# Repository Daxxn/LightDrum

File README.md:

# LightDrum

### Have you ever wanted the drum set to be the loudest thing on stage? Well... this won't do that, but it will be extremely visible!

---

This is my dads christmas present. (I dont even remember how long it's been...) The idea is to lay strings of LEDs on his drum set and control the strings with audio and MIDI signals. With the ability to control more lighting systems through the DMX interface. The other purpose of this project is to learn. To that end, all interface libraries are written by me and are not feature complete or fully tested.

> Current Revision: `REV12`
>
> All revisions before REV8 are early prototypes and are for archival. They are not fully functional or feature complete.

# Renders

## Main PCB

## Interface PCB

## Features

### Output
- 8 Individual LED String Channels
- 1 Amp Rating per Channel
- DMX (RS-485) Interface

## Input
- 1/8" jack Audio
- XLR Balanced Audio
- MIDI
- DMX (RS-485) Interface

## PWM channels

The 8 individual RGB channels are controlled with 3 [PCA9634.](https://www.nxp.com/docs/en/data-sheet/PCA9634.pdf) Providing 8-bit PWM steps per channel with overall brightness and multiplexing.

## Bulk Lighting

The new automitive ECU connector has allowed for more pins, hense, some extra features. This includes 3 linear LED drivers for white COB LEDs. These are very bright and can either be controlled through the user interface, MIDI, or audio.

## Power Management

Each channel includes current monitoring with a high-side power override. This is all to avoid shorts and over-current conditions on the high current 12V supply. Both barrel jacks will need to be used for the LEDs to be activated. Due the large amount of power required, one barrel jack would probably melt.

## Audio Processing

The PCM1821 dual channel 32bit audio ADC handles the audio conversion and is sent to the MCU via I2S. Theres some minor filtering and impedance matching in the analog front-end. However, most of the audio processing will be handled in software.

## User Interface

- 3.2" TFT LCD Display
- Navigation Hat Switch for menu navigation
- Bar Graphs for display of audio levels and current load (or anything else I can think of.)
- 2 Contextual Rotary Encoders
- AND; a reset switch. For when things go horribly wrong.
- MicroSD card slot for loading lighting profiles and other options by the user.

The display contains a full menu to select modes, configure options, and IO. I'm using a Nextion display and their GUI editor for all the menuing. Its not the most performant display but it does allow for easy integration of a reasonably high res, full color screen.

In the future, Im planning to upgrade to a faster STM32 MCU, something like an F7, H5, or H7. Taking advantage of the TouchGFX GUI design software and integrate the screen control into the main MCU. Even with the faster MCU, it will be cheaper and increase screen performance, due to the removal of the Nextion display.

---

## Documentation

- [Docs](./Docs/)

- [Interactive BOMs](./Docs/BOMs/REV10/)

- TODO: Link to a user manual and theory of operation doc.

---

## Firmware installation

### Hardware Requirements

The old firmware was built with the Arduino Framework. The new MCU will be using the ST IDE, toolchain, and HAL (Hardware Abstraction Layer) along with the other required libraries. Im using the STLink programmer due to the much better performance and debugging than the ATTiny USB programmer.

### OLD PIO Configuration

[env:megaUSB] : Uses the built-in programmer. This is only used for the older revisions. (REV1 & REV2)

[env:megaICSP] : Main programming method. Using the ATTiny USB programmer.

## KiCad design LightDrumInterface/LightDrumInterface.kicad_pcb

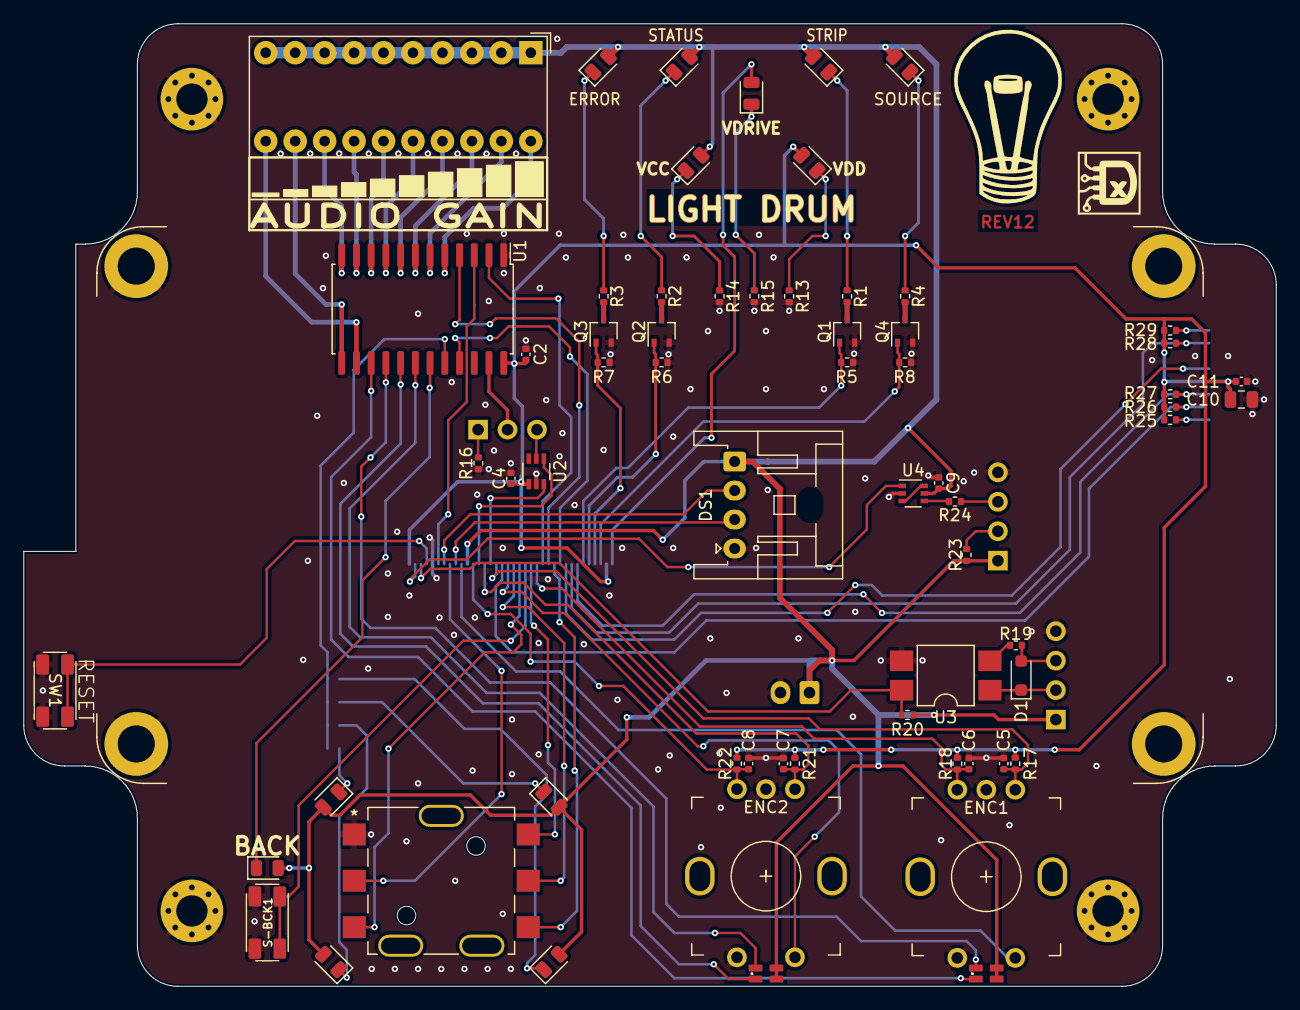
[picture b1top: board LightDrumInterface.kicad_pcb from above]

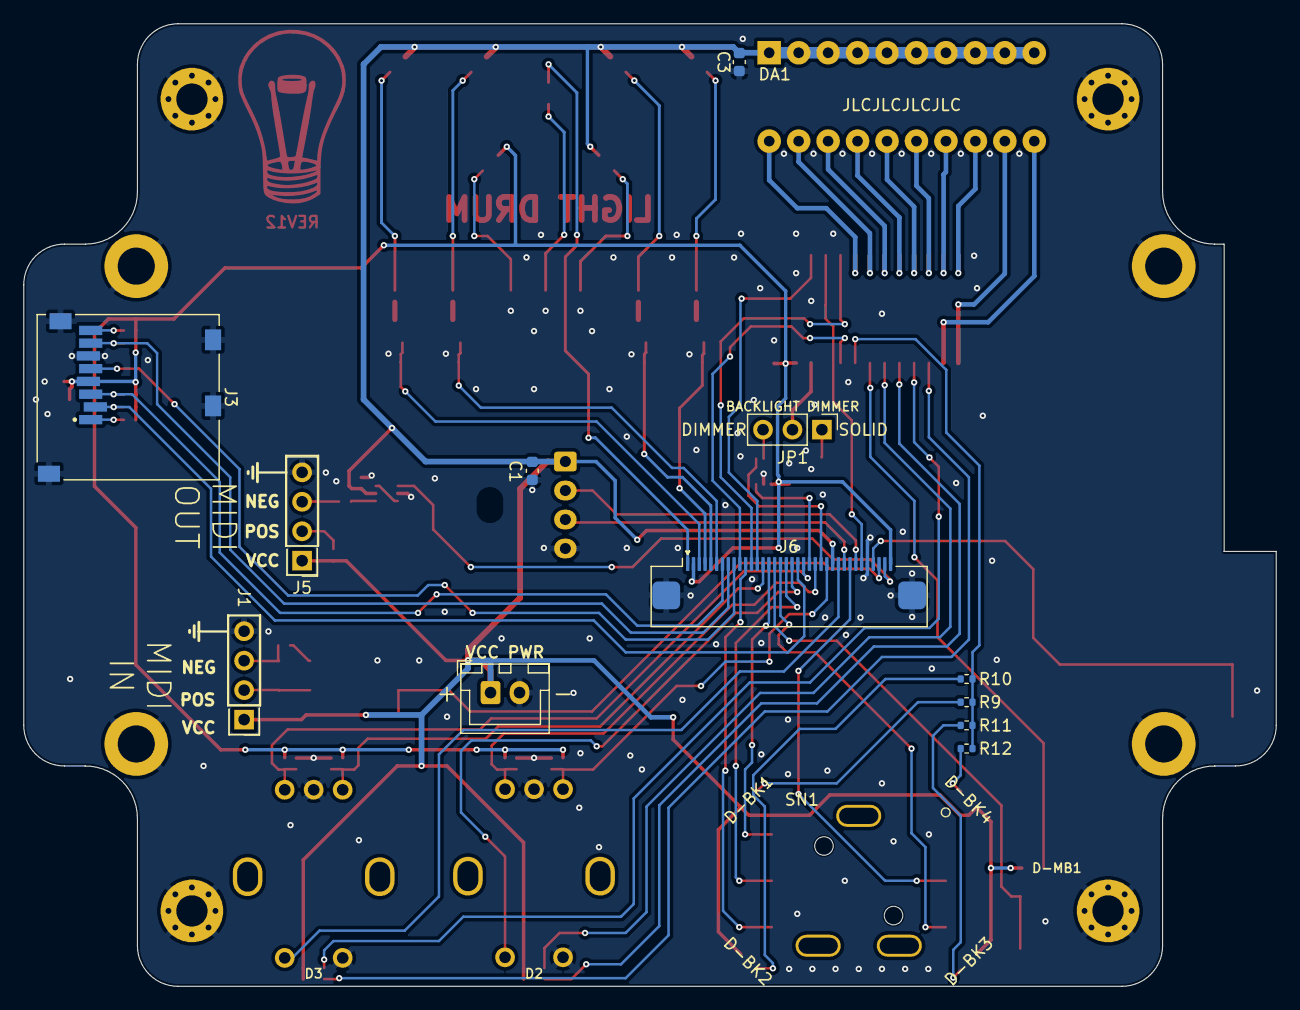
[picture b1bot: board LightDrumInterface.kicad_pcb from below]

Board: 2 copper layers, 108.0 x 83.0 mm, 81 parts (12 on the bottom side), 78 nets.

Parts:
C1, C3: 1uF; C_0603_1608Metric
C2, C4, C5, C6, C7, C8, C9, C11: 100nF; C_0402_1005Metric
C10: 4.7uF; C_0805_2012Metric
D1: 1N4448; D_SOD-323_HandSoldering
D2, D3: APHBM2012QBDSURKC; APHBM-2012
D-AUDIO-SEL1: GREEN; LED_0805_2012Metric
D-BK1, D-BK2, D-BK3, D-BK4: RED; LED_0805_2012Metric
D-DBG1: RED; LED_0805_2012Metric
D-MB1: RED; LED_0805_2012Metric
D-STA1: AMBER; LED_0805_2012Metric
D-STRIP-EN1: GREEN; LED_0805_2012Metric
D-VCC1: BLUE; LED_0805_2012Metric
D-VDD1: BLUE; LED_0805_2012Metric
D-VDRIVE1: BLUE; LED_0805_2012Metric
DA1: LTA-1000HR; HDSP-48xx
DS1: NX4024K032; NX4024K032-RA-S04B
ENC1: Encoder1; PEC11R
ENC2: Encoder2; PEC11R
ENCLOSURE1: LeMotech_Black_ENC-115x90
H1, H2, H3, H4: M2.5; MountingHole_2.7mm_M2.5_Pad_Via
J1: MIDI-IN; PinHeader_1x04_P2.54mm_Vertical
J3: Micro_SD_Card; MEM2061-01-188-00-A
J4: PWR-CONN; JST_XH_B2B-XH-A_Vertical
J5: MIDI-OUT; PinHeader_1x04_P2.54mm_Vertical
J6: 0541323662
JP1: BRT-JMP; PinHeader_1x03_P2.54mm_Vertical
Q1, Q2, Q3, Q4: NX6008NBKWX; SOT-323_SC-70
R1, R4: 100; R_0402_1005Metric
R2, R14, R16: 560; R_0402_1005Metric
R3: 620; R_0402_1005Metric
R5, R6, R7, R8, R17, R18, R20, R21, R22: 10K; R_0402_1005Metric
R9, R10, R11, R12: 300; R_0402_1005Metric
R13: 1.3K; R_0402_1005Metric
R15: 4.7K; R_0402_1005Metric
R19, R23, R24: 220; R_0402_1005Metric
R25, R26, R27, R28, R29: 47K; R_0402_1005Metric
S-BCK1: M-BACK; TL3365AF180QG
SN1: JS5208
SW1: RESET-SW; TL3365AF180QG
U1: STP16CP05; SOIC-24W_7.5x15.4mm_P1.27mm
U2: TPL0401B-10-Q1; Texas_R-PDSO-G6
U3: APC-817A1-SL; SMDIP-4_W7.62mm
U4: 74LVC2G14GW; SOT-363_SC-70-6

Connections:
/AUDIO-SRC-IND: J6.3, Q4.1 (G), R8.1
/DIAG-DEBUG: J6.4, Q3.1 (G), R7.1
/DIAG-STATUS: J6.5, Q2.1 (G), R6.1
/ENC1-A: C5.1, ENC1.A, J6.21, R17.1
/ENC1-B: C6.2, ENC1.B, J6.14, R18.2
/ENC1-SW: ENC1.S1, J6.27
/ENC2-A: C7.1, ENC2.A, J6.23, R21.1
/ENC2-B: C8.2, ENC2.B, J6.25, R22.2
/ENC2-SW: ENC2.S1, J6.19
/GRAPH-CLK: J6.31, U1.3 (CLK)
/GRAPH-LE: J6.12, U1.4 (LE/DM1)
/GRAPH-SDI: J6.13, U1.2 (SDI)
/GRAPH-~OE: J6.10, U1.21 (~OE/DM2)
/I2C-SCLK: J6.22, U2.3 (SCL)
/I2C-SDA: J6.24, U2.4 (SDA)
/MENU-ACT: J6.17, SN1.3 (PUSH)
/MENU-BACK: J6.16, S-BCK1.2 (B)
/MENU-DOWN: J6.11, SN1.6 (DOWN)
/MENU-LEFT: J6.29, SN1.2 (LEFT)
/MENU-RIGHT: J6.18, SN1.5 (RIGHT)
/MENU-UP: J6.15, SN1.4 (UP)
/MIDI-IN: J6.34, R20.1, U3.4
/MIDI-OUT: J6.35, U4.1 (1A)
/NAV-BACKLIGHT: R9.2, R10.2, R11.2, R12.2, U1.20 (~OUT15)
/R-EXT: JP1.2 (C), U1.23 (R-EXT)
/SCR-RX: DS1.3 (RX), J6.28
/SCR-TX: DS1.2 (TX), J6.30
/SD-CD: J3.2 (DAT3/CD), J6.20, R26.2
/SD-CLK: J3.5 (CLK), J6.9
/SD-CMD: J3.3 (CMD), J6.7, R27.2
/SD-D0: J3.7 (DAT0), J6.8, R28.2
/STRIP-PWR: J6.6, Q1.1 (G), R5.1
/~RESET: J6.33, SW1.2 (B)
GND: C1.2, C2.2, C3.2, C4.2, C5.2, C6.1, C7.2, C8.1, C9.2, C10.2, C11.2, DS1.4 (GND), ENC1.C, ENC1.S2, ENC2.C, ENC2.S2, H1.1, H2.1, H3.1, H4.1, J1.4, J3.6 (VSS), J3.9 (SHIELD), J4.2, J5.4, J6.32, J6.M (MNT), Q1.2 (S), Q2.2 (S), Q3.2 (S), Q4.2 (S), R5.2, R6.2, R7.2, R8.2, R13.2, R14.2, R15.2, R16.2, S-BCK1.1 (A), SN1.1 (COM), SW1.1 (A), U1.1 (GND), U2.2 (GND), U3.3, U4.2 (GND)
unnamed: D1.2 (A), J1.3, R19.1
unnamed: D1.1 (K), J1.2, U3.1
unnamed: D2.2 (B-K), U1.17 (~OUT12)
unnamed: D2.3 (R-K), U1.18 (~OUT13)
unnamed: D3.2 (B-K), U1.15 (~OUT10)
unnamed: D3.3 (R-K), U1.16 (~OUT11)
unnamed: D-AUDIO-SEL1.1 (K), R4.1
unnamed: D-BK1.1 (K), R9.1
unnamed: D-BK2.1 (K), R10.1
unnamed: D-BK3.1 (K), R11.1
unnamed: D-BK4.1 (K), R12.1
unnamed: D-DBG1.1 (K), R3.1
unnamed: D-MB1.1 (K), U1.19 (~OUT14)
unnamed: D-STA1.1 (K), R2.1
unnamed: D-STRIP-EN1.1 (K), R1.1
unnamed: D-VCC1.1 (K), R14.1
unnamed: D-VDD1.1 (K), R13.1
unnamed: D-VDRIVE1.1 (K), R15.1
unnamed: J3.8 (DAT1), R29.2
unnamed: J3.1 (DAT2), R25.2
unnamed: J5.2, R23.1
unnamed: J5.3, R24.1
unnamed: JP1.1 (A), R16.1
unnamed: JP1.3 (B), U2.5 (W)
unnamed: Q1.3 (D), R1.2
unnamed: Q2.3 (D), R2.2
unnamed: Q3.3 (D), R3.2
unnamed: Q4.3 (D), R4.2
unnamed: R19.2, U3.2
unnamed: DA1.20, U1.5 (~OUT0)
unnamed: DA1.19, U1.6 (~OUT1)
unnamed: DA1.18, U1.7 (~OUT2)
unnamed: DA1.17, U1.8 (~OUT3)
unnamed: DA1.16, U1.9 (~OUT4)
unnamed: DA1.15, U1.10 (~OUT5)
unnamed: DA1.14, U1.11 (~OUT6)
unnamed: DA1.13, U1.12 (~OUT7)
unnamed: DA1.12, U1.13 (~OUT8)
unnamed: DA1.11, U1.14 (~OUT9)
unnamed: U4.3 (2A), U4.6 (1Y)
unnamed: R24.2, U4.4 (2Y)
VCC: C1.1, C3.1, C9.1, D2.1 (B-A), D2.4 (R-A), D3.1 (B-A), D3.4 (R-A), D-AUDIO-SEL1.2 (A), D-BK1.2 (A), D-BK2.2 (A), D-BK3.2 (A), D-BK4.2 (A), D-DBG1.2 (A), D-MB1.2 (A), D-STA1.2 (A), D-STRIP-EN1.2 (A), D-VCC1.2 (A), DA1.1, DA1.2, DA1.3, DA1.4, DA1.5, DA1.6, DA1.7, DA1.8, DA1.9, DA1.10, DS1.1 (VCC), J1.1, J4.1, J5.1, J6.26, R20.2, R23.2, U4.5 (VCC)
VDD: C2.1, C4.1, C10.1, C11.1, D-VDD1.2 (A), J3.4 (VDD), J6.2, J6.36, R17.2, R18.1, R21.2, R22.1, R25.1, R26.1, R27.1, R28.1, R29.1, U1.24 (VDD), U2.1 (VDD)
Vdrive: D-VDRIVE1.2 (A), J6.1

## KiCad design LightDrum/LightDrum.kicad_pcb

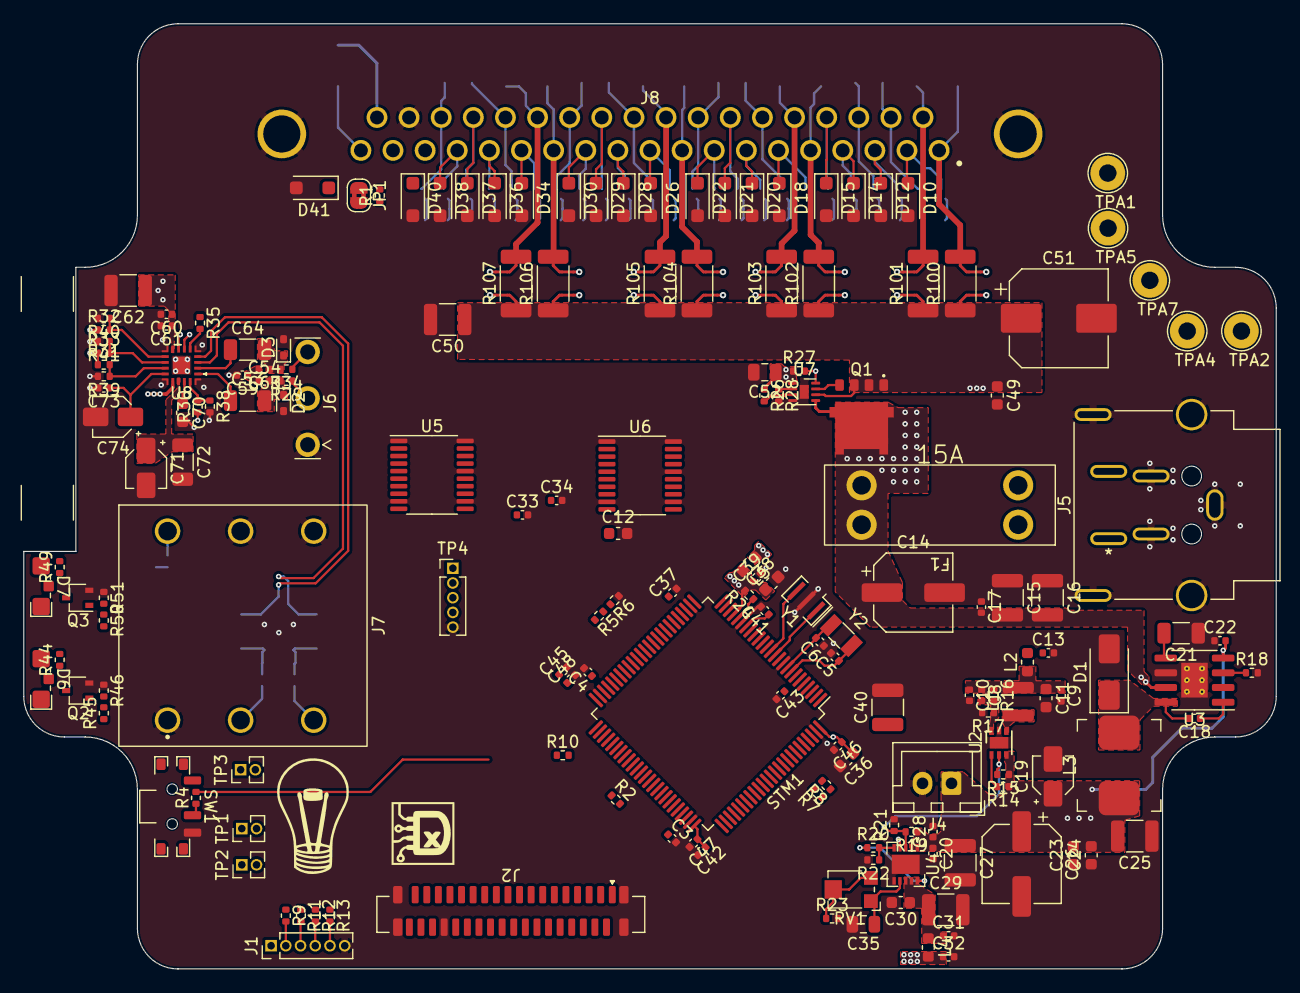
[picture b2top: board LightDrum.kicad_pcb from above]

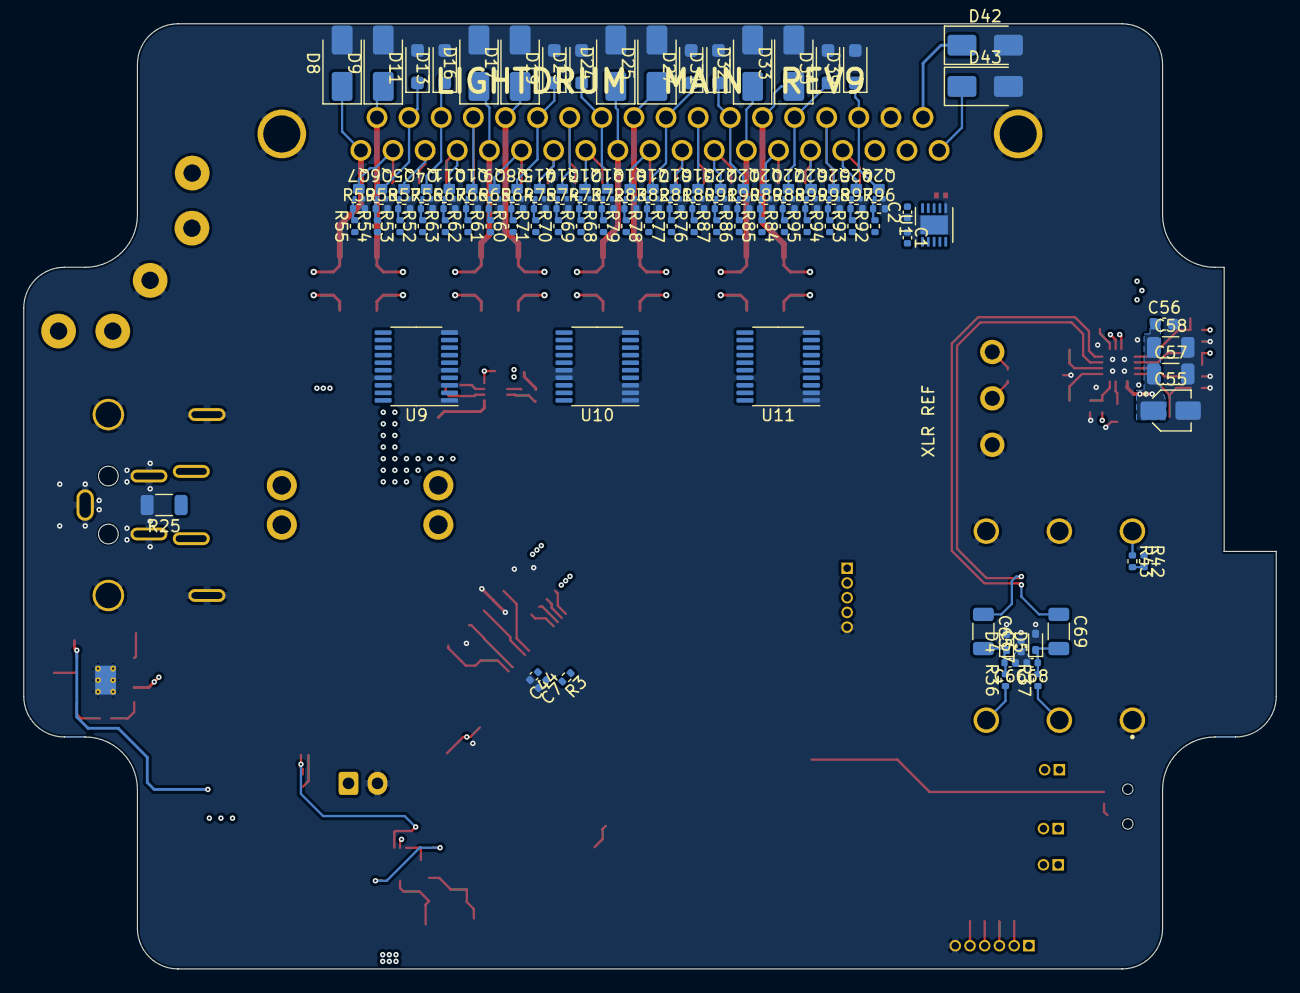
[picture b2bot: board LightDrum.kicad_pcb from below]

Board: 4 copper layers, 108.0 x 81.5 mm, 305 parts (115 on the bottom side), 209 nets.

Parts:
C1, C2, C7, C9, C10, C13, C17, C20, C22, C28, C31, C32, C33, C34, C37, C39, C41, C42, C43, C44, C45, C46, C47, C48, C60, C61, C73: 100nF; C_0402_1005Metric
C3, C4: 2.2uF; C_0402_1005Metric
C5, C6: 15pF; C_0402_1005Metric
C8: 22pF; C_0402_1005Metric
C11, C12, C23, C24, C30, C36, C38, C49, C56, C70: 1uF; C_0603_1608Metric
C14: 47uF; CP_Elec_6.3x7.7
C15, C16, C25, C27, C29, C40, C50, C62: 10uF; C_1210_3225Metric
C18: 10nF; C_0402_1005Metric
C19, C55, C71, C74: 10uF; CP_Elec_3x5.4
C21, C53, C64, C65, C69: 220nF; C_1206_3216Metric
C26: 100uF; CP_Elec_6.3x5.2
C35, C52: 4.7uF; C_0805_2012Metric
C51: 220uF; CP_Elec_8x10
C54, C63, C66, C68: 470pF; C_0402_1005Metric
C57, C58, C72: 100nF C0G; C_1206_3216Metric
C59, C67: 47pF; C_0402_1005Metric
D1: SK36AHE3; D_SMA
D2, D3, D4, D5: CEZ5V6; D_SOD-523
D6: HP IND - BLUE; LTST-S321TBKT
D7: XLR IND - BLUE; LTST-S321TBKT
D8, D9, D16, D17, D24, D25, D32, D33, D42, D43: SMAJ14CA; D_SMA
D10, D11, D12, D13, D14, D15, D18, D19, D20, D21, D22, D23, D26, D27, D28, D29, D30, D31, D34, D35, D36, D37, D38, D39, D40, D41: SMF4L13CA; D_SOD-123F
ENC0: LeMotech_Black_ENC-115x90
F1: 15A; 3557-10
J1: SWD CONN; PinHeader_1x06_P1.27mm_Vertical
J2: 0525593652
J4: PWR-CONN; JST_XH_B2B-XH-A_Vertical
J5: DIN-4-SH; KPJXHT-4S-S
J6: XLR3; CP30082-XLR
J7: SJ-63073E
J8: LED D-SUB; DSUB-37-182-037-113R531
JP1: DMX-RT-JUMP; SolderJumper-2_P1.3mm_Bridged2Bar_RoundedPad1.0x1.5mm
L1: 2.2uH; LQH3NPN
L2, L4, L5: 100nH; L_0603_1608Metric
L3: 22uH; PA4341
Q1: NTMFS5C430NLT1G; POWER-FET-5-DFN
Q2, Q3: NX6008NBKWX; SOT-323_SC-70
Q4, Q5, Q6, Q7, Q8, Q9, Q10, Q11, Q12, Q13, Q14, Q15, Q16, Q17, Q18, Q19, Q20, Q21, Q22, Q23, Q24, Q25, Q26, Q27: PMXB43UNEZ; DFN1010D-3
R1: 120; R_0402_1005Metric
R2, R10: 2.2K; R_0402_1005Metric
R3, R4, R5, R6, R26, R27, R28, R30, R31, R32, R33, R38, R39, R40, R41, R46, R51, R56, R57, R58, R59, R64, R65, R66, R67, R72, R73, R74, R75, R80, R81, R82, R83, R88, R89, R90, R91, R96, R97, R98, R99: 10K; R_0402_1005Metric
R7, R8: 4.7K; R_0402_1005Metric
R9, R11, R12, R13, R29, R34, R35, R36, R37: 22; R_0402_1005Metric
R14, R15, R17, R21, R42: 100K; R_0402_1005Metric
R16: 430K; R_0402_1005Metric
R18: 15K; R_0402_1005Metric
R19: 1.54M; R_0402_1005Metric
R20: 402K; R_0402_1005Metric
R22: 33K; R_0402_1005Metric
R23: 20K; R_0402_1005Metric
R24: 47; R_0402_1005Metric
R25: 10K; R_1206_3216Metric
R43, R45, R50, R52, R53, R54, R55, R60, R61, R62, R63, R68, R69, R70, R71, R76, R77, R78, R79, R84, R85, R86, R87, R92, R93, R94, R95: 100; R_0402_1005Metric
R44, R49: 1K; R_0402_1005Metric
R100, R101, R102, R103, R104, R105, R106, R107: 50m; R_2010_5025Metric
RV1: 4.7K; Bourns_TC33X
STM1: STM32F412VET3; LQFP-100_14x14mm_P0.5mm
SW1: BOOT0; PCM12SMTR
T1, T2, T3, T4, T5, T6, T7, T8, T9, T10, T11, T12, T13, T14, T15, T16: NET-TIE; NetTie-2_SMD_Pad0.25mm
TP1, TP2: I2C TP; PinHeader_1x02_P1.27mm_Vertical
TP3: MIDI TP; PinHeader_1x02_P1.27mm_Vertical
TP4: I2S TP; PinHeader_1x05_P1.27mm_Vertical
TPA1: VDRIVE TP; TestPoint_Loop_D2.54mm_Drill1.5mm_Beaded
TPA2: VCC TP; TestPoint_Loop_D2.54mm_Drill1.5mm_Beaded
TPA4: VDD TP; TestPoint_Loop_D2.54mm_Drill1.5mm_Beaded
TPA5: VDDA TP; TestPoint_Loop_D2.54mm_Drill1.5mm_Beaded
TPA7: GND TP; TestPoint_Loop_D2.54mm_Drill1.5mm_Beaded
U1: STR485; DFN-10-1EP_3x3mm_P0.5mm_EP1.65x2.38mm
U2: AP3401; DFN-6-1EP_2x2mm_P0.65mm_EP1x1.6mm
U3: LM22673-5V; SOIC-8-1EP_3.9x4.9mm_P1.27mm_EP2.29x3mm_ThermalVias
U4: TPS7A94; WSON-10-1EP_3x3mm
U5, U6: INA4181 A2; TSSOP-20_4.4x6.5mm_P0.65mm
U7: SLG55021; TDFN-8-1EP_2x2mm_P0.5mm_EP0.8x1.2mm
U8: PCM1821; TI-WQFN-RTE_(CUSTOM)-20-3x3mm-P0.5mm-EP1_1.4mm
U9, U10, U11: PCA9634_TSSOP20; TSSOP-20_4.4x6.5mm_P0.65mm
Y1: 16MHz; Resonator_SMD_Murata_CSTxExxV-3Pin_3.0x1.1mm
Y2: 32.768KHz; Crystal_SMD_3215-2Pin_3.2x1.5mm

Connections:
+12V: C14.1, C15.2, C16.2, C17.2, F1.2, Q1.5 (D), U3.7 (VIN), U7.5 (D)
/AUDIO INPUTS/JACK+: C65.2, C66.2, D4.1 (K), R36.2
/AUDIO INPUTS/JACK-: C68.1, C69.2, D5.1 (K), R37.2
/AUDIO INPUTS/JACK-IN+: C65.1, U8.3 (IN2+)
/AUDIO INPUTS/JACK-IN-: C69.1, U8.4 (IN2-)
/AUDIO INPUTS/JACK-SW: R42.2, R43.2
/AUDIO INPUTS/XLR+: C53.2, C54.2, D2.1 (K), R29.2
/AUDIO INPUTS/XLR-: C63.1, C64.2, D3.1 (K), R34.2
/AUDIO INPUTS/XLR-IN+: C53.1, U8.1 (IN1+)
/AUDIO INPUTS/XLR-IN-: C64.1, U8.2 (IN1-)
/AUDIO-SRC-IND_{PWM}: J2.3, STM1.4 (TIM9-CH1)
/DIAG-DEBUG_{PWM}: J2.4, STM1.65 (TIM3-CH3)
/DIAG-STATUS_{PWM}: J2.5, STM1.66 (TIM3-CH4)
/DMX+: D40.1 (K), J8.17, R1.2, U1.9 (B)
/DMX-: D41.1 (K), J8.18, JP1.1 (A), U1.8 (A)
/DMX-EN: U1.3 (DE), U1.4 (~RE)
/ENC1-B: J2.10, STM1.85 (PD4)
/ENC2-B: J2.25, STM1.51 (PB12)
/FI2C-SCLK_{S}: R10.2, STM1.54 (I2CFMP1-SCL), TP2.1, U9.18 (SCLK), U9.19 (SDA), U10.18 (SCLK), U11.18 (SCLK)
/FI2C-SDA_{S}: R2.2, STM1.64 (I2CFMP1-SDA), TP2.2, U10.19 (SDA), U11.19 (SDA)
/GRAPH-CLK_{S}: J2.29, STM1.43 (SPI4-SCK)
/GRAPH-LE_{S}: J2.14, STM1.60 (PD13)
/GRAPH-SDI_{S}: J2.31, STM1.5 (SPI4-COPI)
/GRAPH-~OE_{S}: J2.12, STM1.62 (PD15)
/HP-SEL-IND_{PWM}: R45.2, STM1.24 (TIM2-CH2)
/I2C-SCLK_{S}: J2.20, R7.2, STM1.92 (I2C1-SCL), TP1.1
/I2C-SDA_{S}: J2.23, R8.2, STM1.93 (I2C1-SDA), TP1.2
/I2S-CK_{S}: STM1.78 (I2S3-CK), TP4.2, U8.7 (BCLK)
/I2S-SD_{S}: R35.1, STM1.87 (I2S3-SD), TP4.3
/I2S-WS_{S}: STM1.77 (I2S3-WS), TP4.4, U8.8 (FSYNC)
/MICROCONTROLLER/BOOT0_{D}: R4.2, STM1.94 (BOOT0)
/MICROCONTROLLER/BOOT1_{D}: R5.1, R6.2, STM1.37 (BOOT1)
/MICROCONTROLLER/XTAL1: STM1.12 (OSC-IN), Y1.1
/MICROCONTROLLER/XTAL2: STM1.13 (OSC-OUT), Y1.3
/MIDI-IN_{S}: J2.32, STM1.26 (USART2-RX), TP3.1
/MIDI-OUT_{S}: J2.35, STM1.25 (USART2-TX), TP3.2
/POWER/PS-SW_: C18.2, D1.1 (K), L3.1, U3.8 (SW)
/POWER/VREF+: R24.1, STM1.21 (VREF+)
/PWM-~OE_{PWM}: STM1.63 (TIM3-CH1), U9.15 (~OE), U10.15 (~OE), U11.15 (~OE)
/RGB CONTROL/RGB Control 1/LED1-B: D14.1 (K), J8.4, Q11.3 (D)
/RGB CONTROL/RGB Control 1/LED1-B-SIG: R63.1, U9.6 (LED0)
/RGB CONTROL/RGB Control 1/LED1-G: D10.1 (K), J8.2, Q7.3 (D)
/RGB CONTROL/RGB Control 1/LED1-G-SIG: R55.1, U9.14 (LED7)
/RGB CONTROL/RGB Control 1/LED1-R: D12.1 (K), J8.3, Q5.3 (D)
/RGB CONTROL/RGB Control 1/LED1-R-SIG: R53.1, U9.12 (LED5)
/RGB CONTROL/RGB Control 1/LED2-G: D18.1 (K), J8.6, Q9.3 (D)
/RGB CONTROL/RGB Control 1/LED2-G-SIG: R61.1, U9.8 (LED2)
/RGB CONTROL/RGB Control 1/LED5-B: D15.1 (K), J8.23, Q10.3 (D)
/RGB CONTROL/RGB Control 1/LED5-B-SIG: R62.1, U9.7 (LED1)
/RGB CONTROL/RGB Control 1/LED5-G: D11.1 (K), J8.21, Q6.3 (D)
/RGB CONTROL/RGB Control 1/LED5-G-SIG: R54.1, U9.13 (LED6)
/RGB CONTROL/RGB Control 1/LED5-R: D13.1 (K), J8.22, Q4.3 (D)
/RGB CONTROL/RGB Control 1/LED5-R-SIG: R52.1, U9.11 (LED4)
/RGB CONTROL/RGB Control 1/LED6-G: D19.1 (K), J8.25, Q8.3 (D)
/RGB CONTROL/RGB Control 1/LED6-G-SIG: R60.1, U9.9 (LED3)
/RGB CONTROL/RGB Control 2/LED2-B: D22.1 (K), J8.8, Q13.3 (D)
/RGB CONTROL/RGB Control 2/LED2-B-SIG: R69.1, U10.12 (LED5)
/RGB CONTROL/RGB Control 2/LED2-R: D20.1 (K), J8.7, Q15.3 (D)
/RGB CONTROL/RGB Control 2/LED2-R-SIG: R71.1, U10.14 (LED7)
/RGB CONTROL/RGB Control 2/LED3-G: D26.1 (K), J8.10, Q19.3 (D)
/RGB CONTROL/RGB Control 2/LED3-G-SIG: R79.1, U10.6 (LED0)
/RGB CONTROL/RGB Control 2/LED3-R: D28.1 (K), J8.11, Q17.3 (D)
/RGB CONTROL/RGB Control 2/LED3-R-SIG: R77.1, U10.8 (LED2)
/RGB CONTROL/RGB Control 2/LED6-B: D23.1 (K), J8.27, Q12.3 (D)
/RGB CONTROL/RGB Control 2/LED6-B-SIG: R68.1, U10.11 (LED4)
/RGB CONTROL/RGB Control 2/LED6-R: D21.1 (K), J8.26, Q14.3 (D)
/RGB CONTROL/RGB Control 2/LED6-R-SIG: R70.1, U10.13 (LED6)
/RGB CONTROL/RGB Control 2/LED7-G: D27.1 (K), J8.29, Q18.3 (D)
/RGB CONTROL/RGB Control 2/LED7-G-SIG: R78.1, U10.7 (LED1)
/RGB CONTROL/RGB Control 2/LED7-R: D29.1 (K), J8.30, Q16.3 (D)
/RGB CONTROL/RGB Control 2/LED7-R-SIG: R76.1, U10.9 (LED3)
/RGB CONTROL/RGB Control 3/LED3-B: D30.1 (K), J8.12, Q23.3 (D)
/RGB CONTROL/RGB Control 3/LED3-B-SIG: R87.1, U11.14 (LED7)
/RGB CONTROL/RGB Control 3/LED4-B: D38.1 (K), J8.16, Q25.3 (D)
/RGB CONTROL/RGB Control 3/LED4-B-SIG: R93.1, U11.8 (LED2)
/RGB CONTROL/RGB Control 3/LED4-G: D34.1 (K), J8.14, Q21.3 (D)
/RGB CONTROL/RGB Control 3/LED4-G-SIG: R85.1, U11.12 (LED5)
/RGB CONTROL/RGB Control 3/LED4-R: D36.1 (K), J8.15, Q27.3 (D)
/RGB CONTROL/RGB Control 3/LED4-R-SIG: R95.1, U11.6 (LED0)
/RGB CONTROL/RGB Control 3/LED7-B: D31.1 (K), J8.31, Q22.3 (D)
/RGB CONTROL/RGB Control 3/LED7-B-SIG: R86.1, U11.13 (LED6)
/RGB CONTROL/RGB Control 3/LED8-B: D39.1 (K), J8.35, Q24.3 (D)
/RGB CONTROL/RGB Control 3/LED8-B-SIG: R92.1, U11.9 (LED3)
/RGB CONTROL/RGB Control 3/LED8-G: D35.1 (K), J8.33, Q20.3 (D)
/RGB CONTROL/RGB Control 3/LED8-G-SIG: R84.1, U11.11 (LED4)
/RGB CONTROL/RGB Control 3/LED8-R: D37.1 (K), J8.34, Q26.3 (D)
/RGB CONTROL/RGB Control 3/LED8-R-SIG: R94.1, U11.7 (LED1)
/RGB CONTROL/Strip Connector/STRIP-PWR1: D8.1 (K), J8.1, R100.2, T1.2
/RGB CONTROL/Strip Connector/STRIP-PWR2: D16.1 (K), J8.5, R102.2, T5.2
/RGB CONTROL/Strip Connector/STRIP-PWR3: D24.1 (K), J8.9, R104.2, T9.2
/RGB CONTROL/Strip Connector/STRIP-PWR4: D32.1 (K), J8.13, R106.2, T13.2
/RGB CONTROL/Strip Connector/STRIP-PWR5: D9.1 (K), J8.20, R101.2, T2.2
/RGB CONTROL/Strip Connector/STRIP-PWR6: D17.1 (K), J8.24, R103.2, T6.2
/RGB CONTROL/Strip Connector/STRIP-PWR7: D25.1 (K), J8.28, R105.2, T10.2
/RGB CONTROL/Strip Connector/STRIP-PWR8: D33.1 (K), J8.32, R107.2, T14.2
/RGB CONTROL/Strip Current Monitors/S1-CURR+: T3.2, U6.6 (IN+)
/RGB CONTROL/Strip Current Monitors/S1-CURR-: T1.1, U6.7 (IN-)
/RGB CONTROL/Strip Current Monitors/S2-CURR+: T7.2, U6.17 (IN+)
/RGB CONTROL/Strip Current Monitors/S2-CURR-: T5.1, U6.18 (IN-)
/RGB CONTROL/Strip Current Monitors/S3-CURR+: T11.2, U5.6 (IN+)
/RGB CONTROL/Strip Current Monitors/S3-CURR-: T9.1, U5.7 (IN-)
/RGB CONTROL/Strip Current Monitors/S4-CURR+: T15.2, U5.17 (IN+)
/RGB CONTROL/Strip Current Monitors/S4-CURR-: T13.1, U5.18 (IN-)
/RGB CONTROL/Strip Current Monitors/S5-CURR+: T4.2, U6.15 (IN+)
/RGB CONTROL/Strip Current Monitors/S5-CURR-: T2.1, U6.14 (IN-)
/RGB CONTROL/Strip Current Monitors/S6-CURR+: T8.2, U6.4 (IN+)
/RGB CONTROL/Strip Current Monitors/S6-CURR-: T6.1, U6.3 (IN-)
/RGB CONTROL/Strip Current Monitors/S7-CURR+: T12.2, U5.15 (IN+)
/RGB CONTROL/Strip Current Monitors/S7-CURR-: T10.1, U5.14 (IN-)
/RGB CONTROL/Strip Current Monitors/S8-CURR+: T16.2, U5.4 (IN+)
/RGB CONTROL/Strip Current Monitors/S8-CURR-: T14.1, U5.3 (IN-)
/SCR-RX_{S}: J2.19, STM1.68 (USART1-TX)
/SCR-TX_{S}: J2.21, STM1.69 (USART1-RX)
/SD-CD_{S}: J2.34, STM1.82 (PD1)
/SD-CLK_{S}: J2.9, STM1.80 (SDIO-CK)
/SD-CMD_{S}: J2.7, STM1.83 (SDIO-CMD)
/SD-D0_{S}: J2.8, STM1.90 (SDIO-D0)
/STRIP-ESHDN: R26.2, STM1.15 (PC0), U7.3 (~SHDN)
/STRIP-MON_{A}1: STM1.29 (ADC-4), U6.8 (OUT)
/STRIP-MON_{A}2: STM1.32 (ADC-7), U6.19 (OUT)
/STRIP-MON_{A}3: STM1.33 (ADC1-14), U5.8 (OUT)
/STRIP-MON_{A}4: STM1.36 (ADC-9), U5.19 (OUT)
/STRIP-MON_{A}5: STM1.30 (ADC-5), U6.13 (OUT)
/STRIP-MON_{A}6: STM1.31 (ADC-6), U6.2 (OUT)
/STRIP-MON_{A}7: STM1.34 (ADC1-15), U5.13 (OUT)
/STRIP-MON_{A}8: STM1.35 (ADC-8), U5.2 (OUT)
/STRIP-PG: R27.2, STM1.18 (PC3), U7.8 (PG)
/STRIP-PWR: J2.6, R28.1, STM1.81 (PD0), U7.2 (ON)
/VDD-PG: R15.2, R19.2, R21.1, STM1.16 (PC1), U2.2 (PG), U4.3 (EN_UV)
/VDDA-PG: STM1.17 (PC2), U4.4 (PG)
/XLR-SEL-IND_{PWM}: R50.2, STM1.23 (TIM2-CH1)
/~RESET_{C}: C7.1, J2.33, R3.2, R9.1, STM1.14 (~RST)
GND: C1.1, C2.1, C3.2, C4.2, C5.2, C6.1, C7.2, C9.2, C10.2, C11.2, C12.2, C13.2, C14.2, C15.1, C16.1, C17.1, C19.2, C20.2, C21.1, C22.1, C23.1, C24.1, C25.1, C26.2, C27.2, C28.2, C29.2, C30.2, C31.2, C32.2, C33.2, C34.2, C35.2, C36.2, C37.2, C38.2, C39.2, C40.2, C41.2, C42.2, C43.2, C44.2, C45.2, C46.2, C47.2, C48.2, C49.2, C50.2, C51.2, C52.2, C55.2, C56.2, C57.2, C58.2, C59.2, C60.2, C61.2, C62.2, C67.2, C70.2, C71.2, C72.2, C73.2, C74.2, D1.2 (A), D2.2 (A), D3.2 (A), D4.2 (A), D5.2 (A), D8.2 (A), D9.2 (A), D10.2 (A), D11.2 (A), D12.2 (A), D13.2 (A), D14.2 (A), D15.2 (A), D16.2 (A), D17.2 (A), D18.2 (A), D19.2 (A), D20.2 (A), D21.2 (A), D22.2 (A), D23.2 (A), D24.2 (A), D25.2 (A), D26.2 (A), D27.2 (A), D28.2 (A), D29.2 (A), D30.2 (A), D31.2 (A), D32.2 (A), D33.2 (A), D34.2 (A), D35.2 (A), D36.2 (A), D37.2 (A), D38.2 (A), D39.2 (A), D40.2 (A), D41.2 (A), D42.2 (A), D43.2 (A), J1.6, J2.30, J2.M (MNT), J4.2, J5.3, J5.4, J5.M, J6.1, J7.1 (S), J7.5 (TN), J7.6 (RN), J8.0 (PAD), J8.36, Q2.2 (S), Q3.2 (S), Q4.2 (S), Q5.2 (S), Q6.2 (S), Q7.2 (S), Q8.2 (S), Q9.2 (S), Q10.2 (S), Q11.2 (S), Q12.2 (S), Q13.2 (S), Q14.2 (S), Q15.2 (S), Q16.2 (S), Q17.2 (S), Q18.2 (S), Q19.2 (S), Q20.2 (S), Q21.2 (S), Q22.2 (S), Q23.2 (S), Q24.2 (S), Q25.2 (S), Q26.2 (S), Q27.2 (S), R6.1, R17.2, R18.2, R21.2, R22.2, R23.2, R25.2, R28.2, R38.2, R39.2, R40.2, R41.2, R46.1, R51.1, R56.2, R57.2, R58.2, R59.2, R64.2, R65.2, R66.2, R67.2, R72.2, R73.2, R74.2, R75.2, R80.2, R81.2, R82.2, R83.2, R88.2, R89.2, R90.2, R91.2, R96.2, R97.2, R98.2, R99.2, STM1.10 (VSS), STM1.20 (VSSA/VREF-), STM1.27 (VSS), STM1.49 (VSS), STM1.74 (VSS), STM1.99 (VSS), SW1.3 (C), TP4.5, TPA7.1, U1.6 (GND), U1.11 (GND), U2.5 (GND), U2.7 (GND), U3.6 (GND), U3.9 (GND), U4.6 (GND), U4.11 (GND), U5.1 (REF), U5.9 (REF), U5.12 (REF), U5.16, U5.20 (REF), U6.1 (REF), U6.9 (REF), U6.12 (REF), U6.16, U6.20 (REF), U7.4 (GND), U7.9 (GND), U8.5 (GND), U8.10 (GND), U8.15 (GND), U8.20 (GND), U8.21 (GND), U9.1 (A0), U9.3 (A2), U9.5 (A4), U9.10 (GND), U9.17 (A6), U10.1 (A0), U10.2 (A1), U10.3 (A2), U10.10 (GND), U10.16 (A5), U10.17 (A6), U11.1 (A0), U11.2 (A1), U11.5 (A4), U11.10 (GND), U11.17 (A6), Y1.2
unnamed: C8.1, C9.1, C10.1, C11.1, C12.1, L1.2, L2.1, R16.1
unnamed: C54.1, C59.1, C63.2
unnamed: C66.1, C67.1, C68.2
unnamed: D6.1 (K), R44.2
unnamed: D7.1 (K), R49.2
unnamed: F1.1, J5.1, J5.2, R25.1
unnamed: J1.2, R9.2
unnamed: J1.3, R11.2
unnamed: J1.4, R12.2
unnamed: J1.5, R13.2
unnamed: J6.2, R29.1
unnamed: J6.3, R34.1
unnamed: J7.3 (R), R37.1
unnamed: J7.4 (SN), R43.1
unnamed: J7.2 (T), R36.1
unnamed: JP1.2 (B), R1.1
unnamed: Q1.4 (G), U7.7 (G)
unnamed: Q2.3 (D), R44.1
unnamed: Q2.1 (G), R45.1, R46.2
unnamed: Q3.3 (D), R49.1
unnamed: Q3.1 (G), R50.1, R51.2
unnamed: Q4.1 (G), R52.2, R56.1
unnamed: Q5.1 (G), R53.2, R57.1
unnamed: Q6.1 (G), R54.2, R58.1
unnamed: Q7.1 (G), R55.2, R59.1
unnamed: Q8.1 (G), R60.2, R64.1
unnamed: Q9.1 (G), R61.2, R65.1
unnamed: Q10.1 (G), R62.2, R66.1
unnamed: Q11.1 (G), R63.2, R67.1
unnamed: Q12.1 (G), R68.2, R72.1
unnamed: Q13.1 (G), R69.2, R73.1
unnamed: Q14.1 (G), R70.2, R74.1
unnamed: Q15.1 (G), R71.2, R75.1
unnamed: Q16.1 (G), R76.2, R80.1
unnamed: Q17.1 (G), R77.2, R81.1
unnamed: Q18.1 (G), R78.2, R82.1
unnamed: Q19.1 (G), R79.2, R83.1
unnamed: Q20.1 (G), R84.2, R88.1
unnamed: Q21.1 (G), R85.2, R89.1
unnamed: Q22.1 (G), R86.2, R90.1
unnamed: Q23.1 (G), R87.2, R91.1
unnamed: Q24.1 (G), R92.2, R96.1
unnamed: Q25.1 (G), R93.2, R97.1
unnamed: Q26.1 (G), R94.2, R98.1
unnamed: Q27.1 (G), R95.2, R99.1
unnamed: R23.1, RV1.2, RV1.3
unnamed: C4.1, STM1.48 (VCAP1)
unnamed: C3.1, STM1.73 (VCAP2)
unnamed: C5.1, STM1.8 (OSC32-IN), Y2.1
unnamed: C6.2, STM1.9 (OSC32-OUT), Y2.2
unnamed: R4.1, SW1.2 (B)
unnamed: R14.2, U2.1 (EN)
unnamed: C8.2, R16.2, R17.1, U2.6 (FB)
unnamed: L1.1, U2.4 (LX)
unnamed: C18.1, U3.1 (BOOT)
unnamed: R18.1, U3.3 (IADJ)
unnamed: C21.2, U3.5 (SS)
unnamed: R20.2, R22.1, U4.5 (FB_PG)
unnamed: C35.1, RV1.1, U4.7 (NR/SS)
unnamed: C29.1, C30.1, C31.1, L4.1, R20.1, U4.8 (SNS), U4.9 (OUT), U4.10 (OUT)
unnamed: C71.1, C72.1, U8.17 (AREG)
unnamed: C73.1, C74.1, U8.14 (DREG)
unnamed: R30.2, R38.1, U8.19 (FMT0)
unnamed: R33.2, R41.1, U8.12 (MD0)
unnamed: R32.2, R40.1, U8.11 (MD1)
unnamed: R31.2, R39.1, U8.13 (MSZ)
unnamed: R35.2, U8.6 (SDOUT)
unnamed: C70.1, U8.18 (VREF)
SWDCLK_{D}: R11.1, STM1.76 (SWCLK)
SWDIO_{D}: R12.1, STM1.72 (SWDIO)
SWO_{D}: R13.1, STM1.89 (SWO)
VAA: C32.1, C55.1, C56.1, C57.1, C58.1, L4.2, U8.16 (VDDA)
VCC: C19.1, C20.1, C22.2, C23.2, C24.2, C25.2, C26.1, C27.1, C28.1, C52.1, D6.2 (A), D7.2 (A), D42.1 (K), J2.24, J4.1, J8.37, L3.2, R14.1, R15.1, R19.1, R26.1, R27.1, TPA2.1, U2.3 (VIN), U3.4 (FB), U4.1 (IN), U4.2 (IN), U7.1 (VCC)
VDD: C1.2, C2.2, C13.1, C36.1, C37.1, C40.1, C41.1, C42.1, C43.1, C44.1, C45.1, C46.1, C47.1, C48.1, C60.1, C61.1, C62.1, D43.1 (K), J1.1, J2.2, J2.36, J8.19, L2.2, L5.1, R2.1, R3.1, R5.2, R7.1, R8.1, R10.1, R30.1, R31.1, R32.1, R33.1, R42.1, STM1.6 (VBAT), STM1.11 (VDD), STM1.19 (VDD), STM1.28 (VDD), STM1.50 (VDD), STM1.75 (VDD), STM1.100 (VDD), SW1.1 (A), TP4.1, TPA4.1, U1.1 (V_{L}), U1.7 (SLR), U1.10 (VCC), U8.9 (VDD), U9.2 (A1), U9.4 (A3), U9.16 (A5), U9.20 (VCC), U10.4 (A3), U10.5 (A4), U10.20 (VCC), U11.3 (A2), U11.4 (A3), U11.16 (A5), U11.20 (VCC)
VDDA: C33.1, C34.1, C38.1, C39.1, L5.2, R24.2, STM1.22 (VDDA), TPA5.1, U5.5, U6.5
Vdrive: C49.1, C50.1, C51.1, J2.1, Q1.1 (S), Q1.2 (S), Q1.3 (S), R100.1, R101.1, R102.1, R103.1, R104.1, R105.1, R106.1, R107.1, T3.1, T4.1, T7.1, T8.1, T11.1, T12.1, T15.1, T16.1, TPA1.1, U7.6 (S)

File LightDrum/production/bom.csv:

Designator,Footprint,Quantity,Value,LCSC Part #
"C1, C10, C13, C17, C2, C20, C22, C28, C31, C32, C33, C34, C37, C39, C41, C42, C43, C44, C45, C46, C47, C48, C60, C61, C7, C73, C9",0402,27,100nF,
"C11, C12, C23, C24, C30, C36, C38, C49, C56, C70",0603,10,1uF,
C14,CP_Elec_6.3x7.7,1,47uF,
"C15, C16, C25, C27, C29, C40, C50, C62",1210,8,10uF,
C18,0402,1,10nF,
"C19, C55, C71, C74",CP_Elec_3x5.4,4,10uF,
"C21, C53, C64, C65, C69",1206,5,220nF,
C26,CP_Elec_6.3x5.2,1,100uF,
"C3, C4",0402,2,2.2uF,
"C35, C52",0805,2,4.7uF,
"C5, C6",0402,2,15pF,
C51,CP_Elec_8x10,1,220uF,
"C54, C63, C66, C68",0402,4,470pF,
"C57, C58, C72",1206,3,100nF C0G,
"C59, C67",0402,2,47pF,
C8,0402,1,22pF,
D1,D_SMA,1,SK36AHE3,
"D10, D11, D12, D13, D14, D15, D18, D19, D20, D21, D22, D23, D26, D27, D28, D29, D30, D31, D34, D35, D36, D37, D38, D39, D40, D41",D_SOD-123F,26,SMF4L13CA,
"D16, D17, D24, D25, D32, D33, D42, D43, D8, D9",D_SMA,10,SMAJ14CA,
"D2, D3, D4, D5",D_SOD-523,4,CEZ5V6,
D6,LTST-S321TBKT,1,HP IND - BLUE,
D7,LTST-S321TBKT,1,XLR IND - BLUE,
ENC0,LeMotech_Black_ENC-115x90,1,LeMotech_Black_ENC-115x90,
F1,3557-10,1,15A,
"H1, H2, H3, H4",MountingHole_2.7mm_M2.5_Pad_Via,4,M2.5,
J1,PinHeader_1x06_P1.27mm_Vertical,1,SWD CONN,
J2,0525593652,1,0525593652,
J4,JST_XH_B2B-XH-A_Vertical,1,PWR-CONN,
J5,KPJXHT-4S-S,1,DIN-4-SH,
J6,CP30082-XLR,1,XLR3,
J7,SJ-63073E,1,SJ-63073E,
J8,DSUB-37-182-037-113R531,1,LED D-SUB,
JP1,SolderJumper-2_P1.3mm_Bridged2Bar_RoundedPad1.0x1.5mm,1,DMX-RT-JUMP,
L1,LQH3NPN,1,2.2uH,
L2,1210,1,100nH,
L3,PA4341,1,22uH,
"L4, L5",0603,2,100nH,
Q1,POWER-FET-5-DFN,1,NTMFS5C430NLT1G,
"Q10, Q11, Q12, Q13, Q14, Q15, Q16, Q17, Q18, Q19, Q20, Q21, Q22, Q23, Q24, Q25, Q26, Q27, Q4, Q5, Q6, Q7, Q8, Q9",DFN1010D-3,24,PMXB43UNEZ,
"Q2, Q3",SOT-323_SC-70,2,NX6008NBKWX,
R1,0402,1,120,
"R10, R2",0402,2,2.2K,
"R100, R101, R102, R103, R104, R105, R106, R107",2010,8,50m,
"R11, R12, R13, R29, R34, R35, R36, R37, R9",0402,9,22,
"R14, R15, R17, R21, R42",0402,5,100K,
R16,0402,1,430K,
R18,0402,1,15K,
R19,0402,1,1.54M,
R20,0402,1,402K,
R22,0402,1,33K,
R23,0402,1,20K,
R24,0402,1,47,
R25,1206,1,10K,
"R26, R27, R28, R3, R30, R31, R32, R33, R38, R39, R4, R40, R41, R46, R5, R51, R56, R57, R58, R59, R6, R64, R65, R66, R67, R72, R73, R74, R75, R80, R81, R82, R83, R88, R89, R90, R91, R96, R97, R98, R99",0402,41,10K,
"R43, R45, R50, R52, R53, R54, R55, R60, R61, R62, R63, R68, R69, R70, R71, R76, R77, R78, R79, R84, R85, R86, R87, R92, R93, R94, R95",0402,27,100,
"R44, R49",0402,2,1K,
"R7, R8",0402,2,4.7K,
RV1,Bourns_TC33X,1,4.7K,
STM1,LQFP-100_14x14mm_P0.5mm,1,STM32F412VET3,
SW1,PCM12SMTR,1,BOOT0,
"T1, T10, T11, T12, T13, T14, T15, T16, T2, T3, T4, T5, T6, T7, T8, T9",NetTie-2_SMD_Pad0.25mm,16,NET-TIE,
"TP1, TP2",PinHeader_1x02_P1.27mm_Vertical,2,I2C TP,
TP3,PinHeader_1x02_P1.27mm_Vertical,1,MIDI TP,
TP4,PinHeader_1x05_P1.27mm_Vertical,1,I2S TP,
TPA1,TestPoint_Loop_D2.54mm_Drill1.5mm_Beaded,1,VDRIVE TP,
TPA2,TestPoint_Loop_D2.54mm_Drill1.5mm_Beaded,1,VCC TP,
TPA4,TestPoint_Loop_D2.54mm_Drill1.5mm_Beaded,1,VDD TP,
TPA5,TestPoint_Loop_D2.54mm_Drill1.5mm_Beaded,1,VDDA TP,
TPA7,TestPoint_Loop_D2.54mm_Drill1.5mm_Beaded,1,GND TP,
U1,DFN-10-1EP_3x3mm_P0.5mm_EP1.65x2.38mm,1,STR485,
"U10, U11, U9",TSSOP-20_4.4x6.5mm_P0.65mm,3,PCA9634_TSSOP20,
U2,DFN-6-1EP_2x2mm_P0.65mm_EP1x1.6mm,1,AP3401,
U3,SOIC-8-1EP_3.9x4.9mm_P1.27mm_EP2.29x3mm_ThermalVias,1,LM22673-5V,
U4,WSON-10-1EP_3x3mm,1,TPS7A94,
"U5, U6",TSSOP-20_4.4x6.5mm_P0.65mm,2,INA4181 A2,
U7,TDFN-8-1EP_2x2mm_P0.5mm_EP0.8x1.2mm,1,SLG55021,
U8,TI-WQFN-RTE_(CUSTOM)-20-3x3mm-P0.5mm-EP1_1.4mm,1,PCM1821,
Y1,Resonator_SMD_Murata_CSTxExxV-3Pin_3.0x1.1mm,1,16MHz,
Y2,Crystal_SMD_3215-2Pin_3.2x1.5mm,1,32.768KHz,

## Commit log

2022-03-01 Fix Menu System
2022-03-01 Fix performance issues
2022-03-01 Add License
2022-03-01 Add gerber and PCB files
2022-03-02 Fix LED driver bugs and test PWM lines
2022-03-05 Remove old menu attempts
2022-04-30 REV3 Initial Commit
2022-06-17 Reorganize project files and add docs
2022-06-17 Move README to main dir
2022-06-17 Fix LED Conn Pinout table
2022-06-18 Add PWM docs and fix bugs
2022-06-19 Fix PCA9634 Drivers
2022-06-19 Fix bugs and add conversion layer for LED strips
2022-06-25 Fix Documentation and add older revisions
2022-10-09 Fix integration bugs (Screen, I2C, Ind, ADC)
2022-10-15 Add REV6 docs and fix some bugs
2023-01-01 Add docs
2023-01-01 Add the rest of the docs
2023-01-01 Add firmware code
2023-01-01 Replace interface harnesses with FPC cable
2023-01-01 Add extra vcc pin to FPC conn
2023-01-02 Add docs and gerbers for REV7
2023-01-02 Remove un-zipped gerber files for REV5
2023-01-02 modify gitignore
2023-01-02 Add logo to interface PCB
2023-01-07 Minor code edits
2023-01-08 Replace screen (WIP)
2023-01-08 Replaced display and FPC cable
2023-01-08 Update readme and REV7 renders
2023-01-14 First pass over schematic (WIP)
2023-01-14 Clean up and remove old files
2023-01-15 General component placement
2023-01-15 Replace with smaller case (WIP)
2023-01-16 Simplify analog power supply and add some routing
2023-01-21 Remove RTC and battery
2023-01-21 Swap mcu again... (WIP)
2023-01-22 Replace barrel jacks with proper DIN4 conn and more
2023-01-22 Replace old MOSFETs with a more compact package
2023-01-23 Lock REV8 Layout and send to PCB MNF
2023-01-23 Update readme and add new renders
2023-01-28 Setup initial IC config and pinout
2023-01-28 Replace old MCU W/ STM32F412
2023-01-29 Replace MCU finished. REV9
2023-01-29 Fix DRC issues - Main Board - REV9
2023-01-29 interface layout completed - REV6
2023-01-30 Main and Interface PCBs locked - REV9
2023-01-30 Update readme and crop renders
2023-02-05 Add main page to sch and xlr audio input diff-amp
2023-02-06 Change flags in sch
2023-02-12 Start REV 10 - Fix small issues
2023-02-13 Add ind shift reg driver and fix LED MOSFET pin mixup
2023-02-13 Add button code and configure IRQs
2023-02-13 Update display colors file
2023-02-13 Fix display colors save file
2023-03-10 Update save files to KiCad 7
2023-03-10 Fix BOM generator options
2023-03-10 Fix readme
2023-04-03 Cleaning tracked files
2023-04-03 Finish firmware cleanup
2023-04-03 Add RTC
2023-04-03 Fix drill reference
2023-04-03 Replace relays and SWD conn
2023-04-09 Preliminary schematic lock - Starting PCB layout
2023-04-10 Component placement complete
2023-04-12 Continuing layout
2023-04-13 First draft layout almost complete
2023-04-15 PCB Lock REV11
2023-04-17 Minor fixes and cleanup - REV11
2023-04-30 Fix backwards Connector - Initial Testing
2023-04-30 replace STM32 package with 100-BGA
2023-05-08 Replace DSub with much better ECU conn
2023-05-08 Untrack and remove 3D model files
2023-05-08 Rename old LED strip pinout file
2023-05-08 Add REV12 renders and update the readme
2023-05-08 Organize old files and generate interface gerbers
2023-05-08 Fix MCU pinout in IDE
2023-05-08 Firmware fixes
2023-05-09 Fix schematic layout
2023-05-09 Add code for PCA9634 and gen gerbers
2023-05-21 (WIP) REV12 Testing and firmware dev
2023-05-28 add screen control and more display layout
2023-05-29 fix screen ctrl bugs and add I2S data transfer
2024-05-16 old version save
2024-05-16 REV13 - Revert to KiCAD 7
2024-05-16 REV13 - Update to KiCAD 8
